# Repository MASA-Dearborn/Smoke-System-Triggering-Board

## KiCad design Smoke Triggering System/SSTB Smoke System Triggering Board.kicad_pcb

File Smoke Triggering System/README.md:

# Smoke-System-Triggering-Board

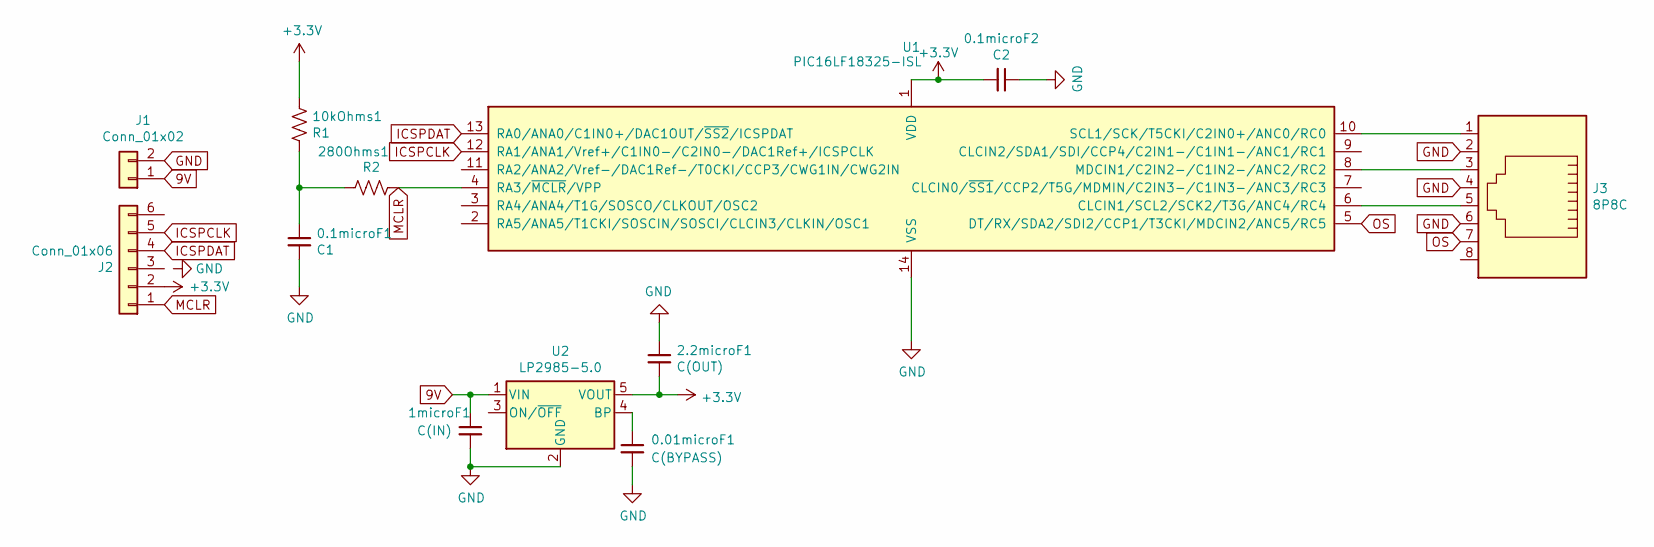
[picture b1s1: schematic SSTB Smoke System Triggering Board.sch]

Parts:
0.1microF1: C1; C_0805_2012Metric
0.01microF1: C(BYPASS); C_0805_2012Metric
0.1microF2: C2; C_0805_2012Metric
1microF1: C(IN); C_0805_2012Metric
2.2microF1: C(OUT); C_0805_2012Metric
10kOhms1: R1; R_0805_2012Metric
280Ohms1: R2; R_0805_2012Metric
J1: Conn_01x02; 1-1123723-2
J2: Conn_01x06; 1735446-6
J3: 8P8C; 1735446-8
U1: PIC16LF18325-ISL; SOIC-14_3.9x8.7mm_P1.27mm
U2: LP2985-5.0; SOT-23-5

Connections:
9V: 1microF1.1, J1.1, U2.1 (VIN)
+3V3: 0.1microF2.2, 2.2microF1.2, 10kOhms1.1, J2.2, U1.1 (VDD), U2.5 (VOUT)
GND: 0.1microF1.2, 0.01microF1.2, 0.1microF2.1, 1microF1.2, 2.2microF1.1, J1.2, J3.2, J3.4, J3.6, U1.14 (VSS), U2.2 (GND)
ICSPCLK: J2.5, U1.12 (RA1/ANA1/Vref+/C1IN0-/C2IN0-/DAC1Ref+/I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)
ICSPDAT: J2.4, U1.13 (RA0/ANA0/C1IN0+/DAC1OUT/~SS2~/ICSPDAT)
MCLR: 280Ohms1.2, J2.1, U1.4 (RA3/~MCLR~/VPP)
unnamed: 0.01microF1.1, U2.4 (BP)
unnamed: 0.1microF1.1, 10kOhms1.2, 280Ohms1.1
unnamed: J3.1, U1.10 (SCL1/SCK/T5CKI/C2IN0+/ANC0/RC0)
unnamed: J3.3, U1.8 (MDCIN1/C2IN2-/C1IN2-/ANC2/RC2)
unnamed: J3.5, U1.6 (CLCIN1/SCL2/SCK2/T3G/ANC4/RC4)
OS: J3.7, U1.5 (DT/RX/SDA2/SDI2/CCP1/T3CKI/MDCIN2/ANC5/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)

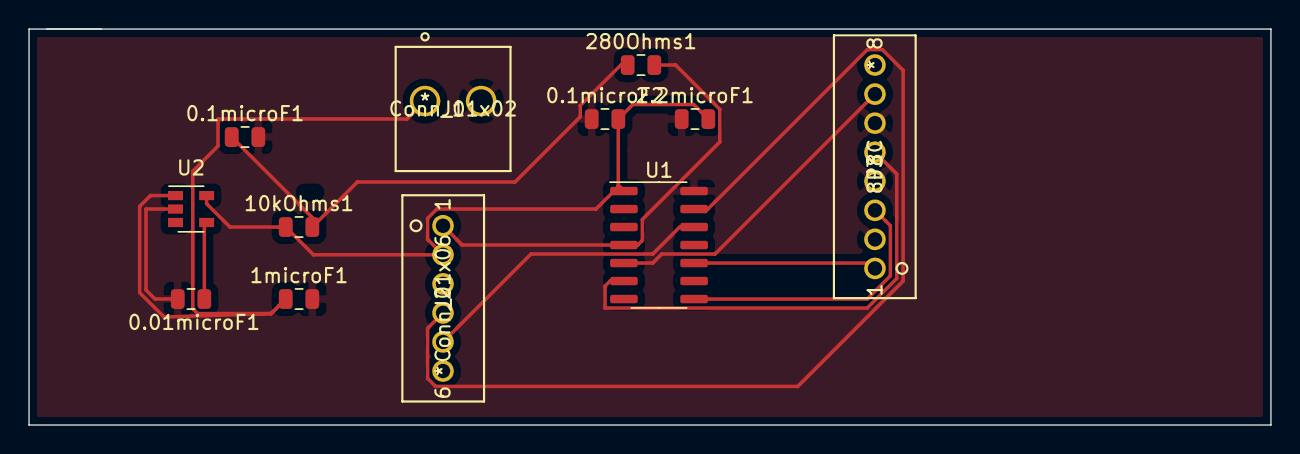
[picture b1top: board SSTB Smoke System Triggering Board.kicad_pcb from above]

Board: 2 copper layers, 87.6 x 27.9 mm, 12 parts (0 on the bottom side), 12 nets.

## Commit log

2020-02-27 inital commit

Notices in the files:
parts and their libraries:
Copyright 2016 Accelerated Designs. All rights reserved.
